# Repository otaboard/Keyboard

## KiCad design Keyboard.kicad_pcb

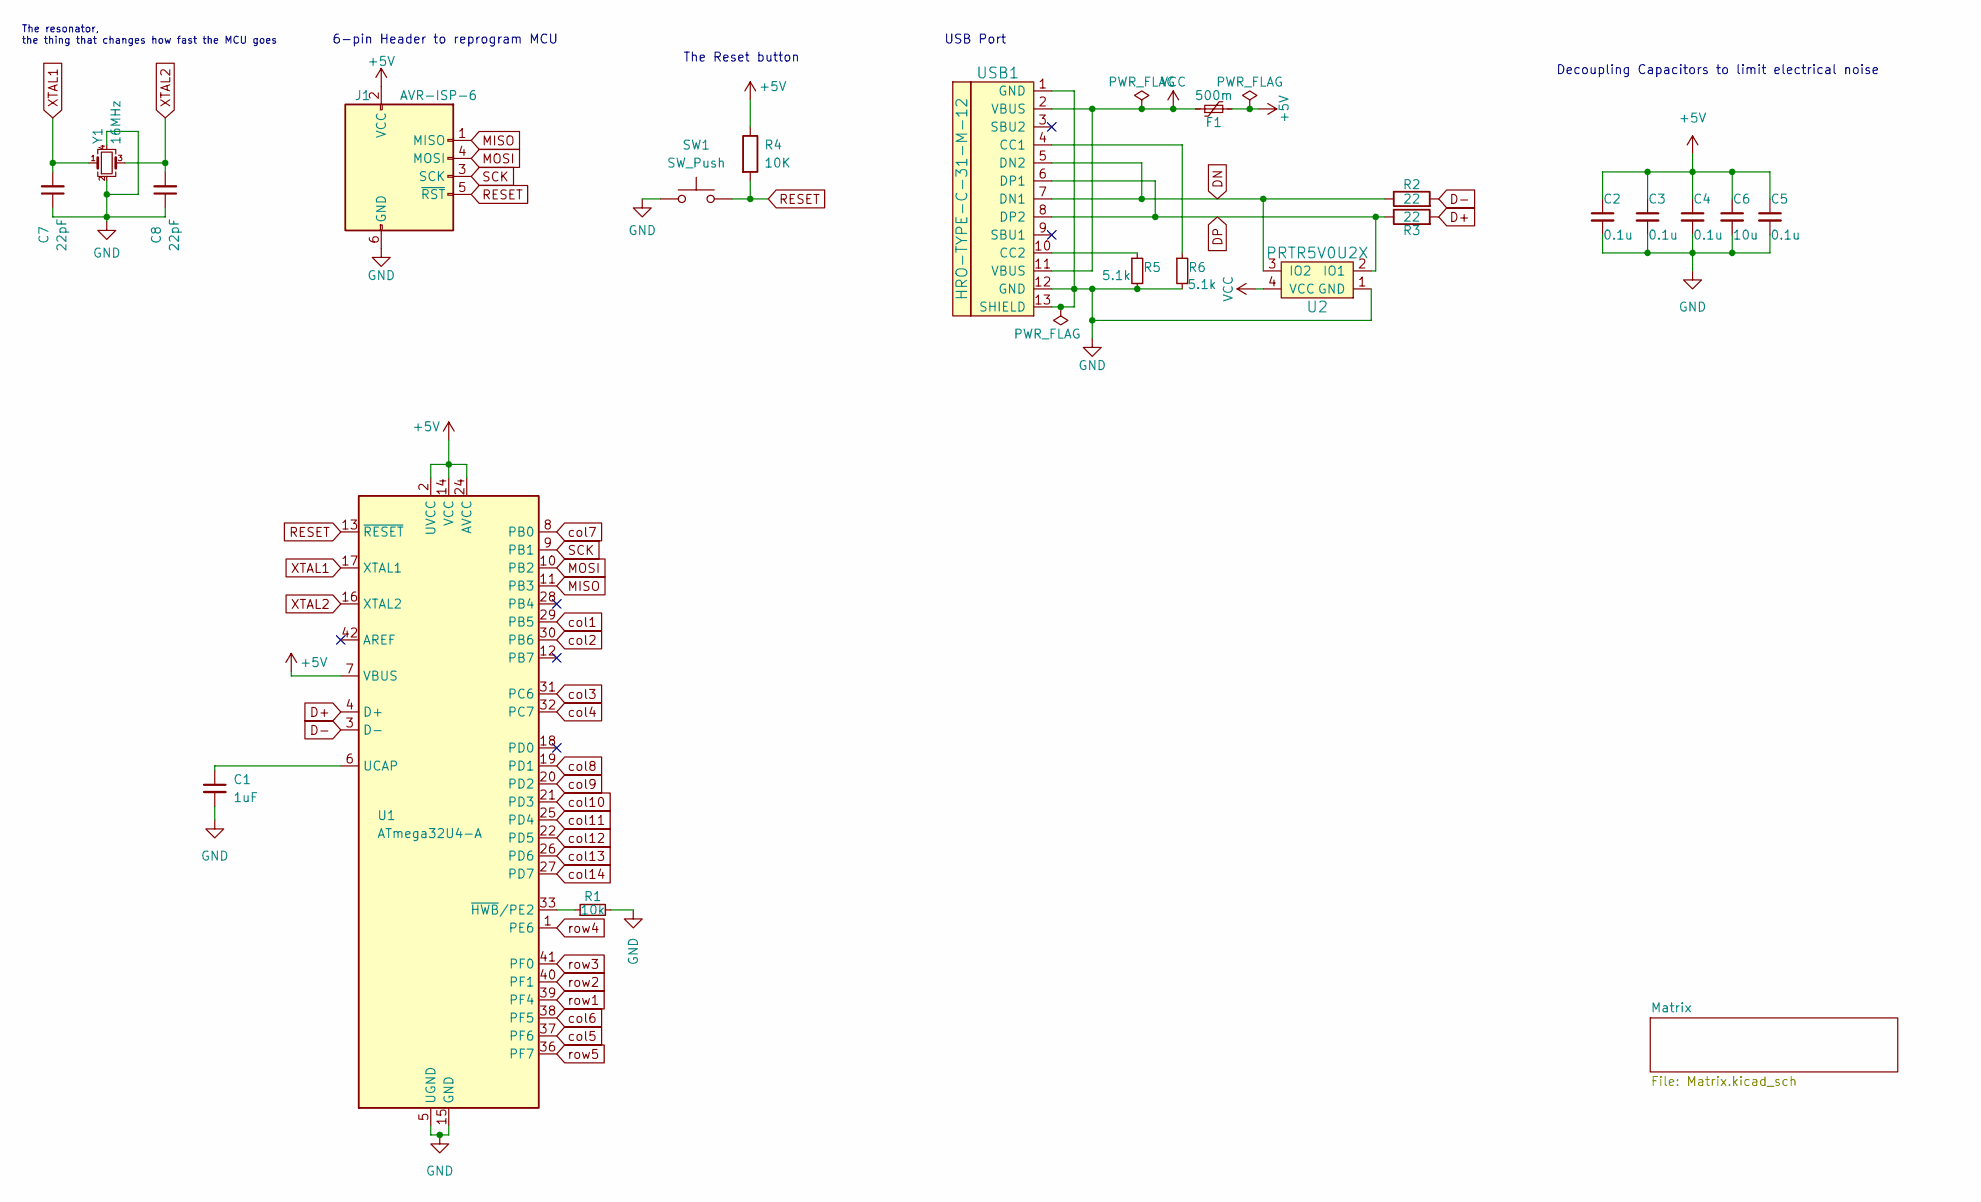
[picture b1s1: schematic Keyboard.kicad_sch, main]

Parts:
C1: 1uF; C_0805_2012Metric_Pad1.18x1.45mm_HandSolder
C2, C3, C4, C5: 0.1u; C_0805_2012Metric_Pad1.18x1.45mm_HandSolder
C6: 10u; C_0805_2012Metric_Pad1.18x1.45mm_HandSolder
C7, C8: 22pF; C_0805_2012Metric_Pad1.18x1.45mm_HandSolder
F1: 500m; Fuse_1206_3216Metric_Pad1.42x1.75mm_HandSolder
J1: AVR-ISP-6; Reset_Pretty-Mask
R1: 10k; R_0805_2012Metric_Pad1.20x1.40mm_HandSolder
R2, R3: 22; R_0805_2012Metric_Pad1.20x1.40mm_HandSolder
R4: 10K; R_0805_2012Metric_Pad1.20x1.40mm_HandSolder
R5, R6: 5.1k; R_0805_2012Metric_Pad1.20x1.40mm_HandSolder
SW1: SW_Push; SW_SPST_SKQG_WithStem
U1: ATmega32U4-A; TQFP-44_10x10mm_P0.8mm
U2: PRTR5V0U2X; SOT143B
USB1: HRO-TYPE-C-31-M-12; HRO-TYPE-C-31-M-12-HandSoldering
Y1: 16MHz; Crystal_SMD_3225-4Pin_3.2x2.5mm_HandSoldering

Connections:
+5V: C2.1, C3.1, C4.1, C5.1, C6.1, F1.2, J1.2 (VCC), R4.1, U1.2 (UVCC), U1.7 (VBUS), U1.14 (VCC), U1.24 (AVCC), U1.34 (VCC), U1.44 (AVCC)
D+: R3.2, U1.4 (D+)
D-: R2.2, U1.3 (D-)
DN: R2.1, U2.3 (IO2), USB1.5 (DN2), USB1.7 (DN1)
DP: R3.1, U2.2 (IO1), USB1.6 (DP1), USB1.8 (DP2)
GND: C1.2, C2.2, C3.2, C4.2, C5.2, C6.2, C7.1, C8.1, J1.6 (GND), R1.2, R5.2, R6.2, SW1.1, U1.5 (UGND), U1.15 (GND), U1.23 (GND), U1.35 (GND), U1.43 (GND), U2.1 (GND), USB1.1 (GND), USB1.12 (GND), USB1.13 (SHIELD), Y1.2, Y1.4
MISO: J1.1 (MISO), U1.11 (PB3)
MOSI: J1.4 (MOSI), U1.10 (PB2)
unnamed: C1.1, U1.6 (UCAP)
unnamed: R1.1, U1.33 (~HWB/PE2)
unnamed: R5.1, USB1.10 (CC2)
unnamed: R6.1, USB1.4 (CC1)
RESET: J1.5 (~RST), R4.2, SW1.2, U1.13 (~RESET)
SCK: J1.3 (SCK), U1.9 (PB1)
VCC: F1.1, U2.4 (VCC), USB1.2 (VBUS), USB1.11 (VBUS)
XTAL1: C7.2, U1.17 (XTAL1), Y1.1
XTAL2: C8.2, U1.16 (XTAL2), Y1.3
col1: U1.29 (PB5); also elsewhere on the board
col2: U1.30 (PB6); also elsewhere on the board
col3: U1.31 (PC6); also elsewhere on the board
col4: U1.32 (PC7); also elsewhere on the board
col5: U1.37 (PF6); also elsewhere on the board
col6: U1.38 (PF5); also elsewhere on the board
col7: U1.8 (PB0); also elsewhere on the board
col8: U1.19 (PD1); also elsewhere on the board
col9: U1.20 (PD2); also elsewhere on the board
col10: U1.21 (PD3); also elsewhere on the board
col11: U1.25 (PD4); also elsewhere on the board
col12: U1.22 (PD5); also elsewhere on the board
col13: U1.26 (PD6); also elsewhere on the board
col14: U1.27 (PD7); also elsewhere on the board
row1: U1.39 (PF4); also elsewhere on the board
row2: U1.40 (PF1); also elsewhere on the board
row3: U1.41 (PF0); also elsewhere on the board
row4: U1.1 (PE6); also elsewhere on the board
row5: U1.36 (PF7); also elsewhere on the board

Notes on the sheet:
6-pin Header to reprogram MCU
USB Port
The resonator, the thing that changes how fast the MCU goes
Decoupling Capacitors to limit electrical noise
The Reset button

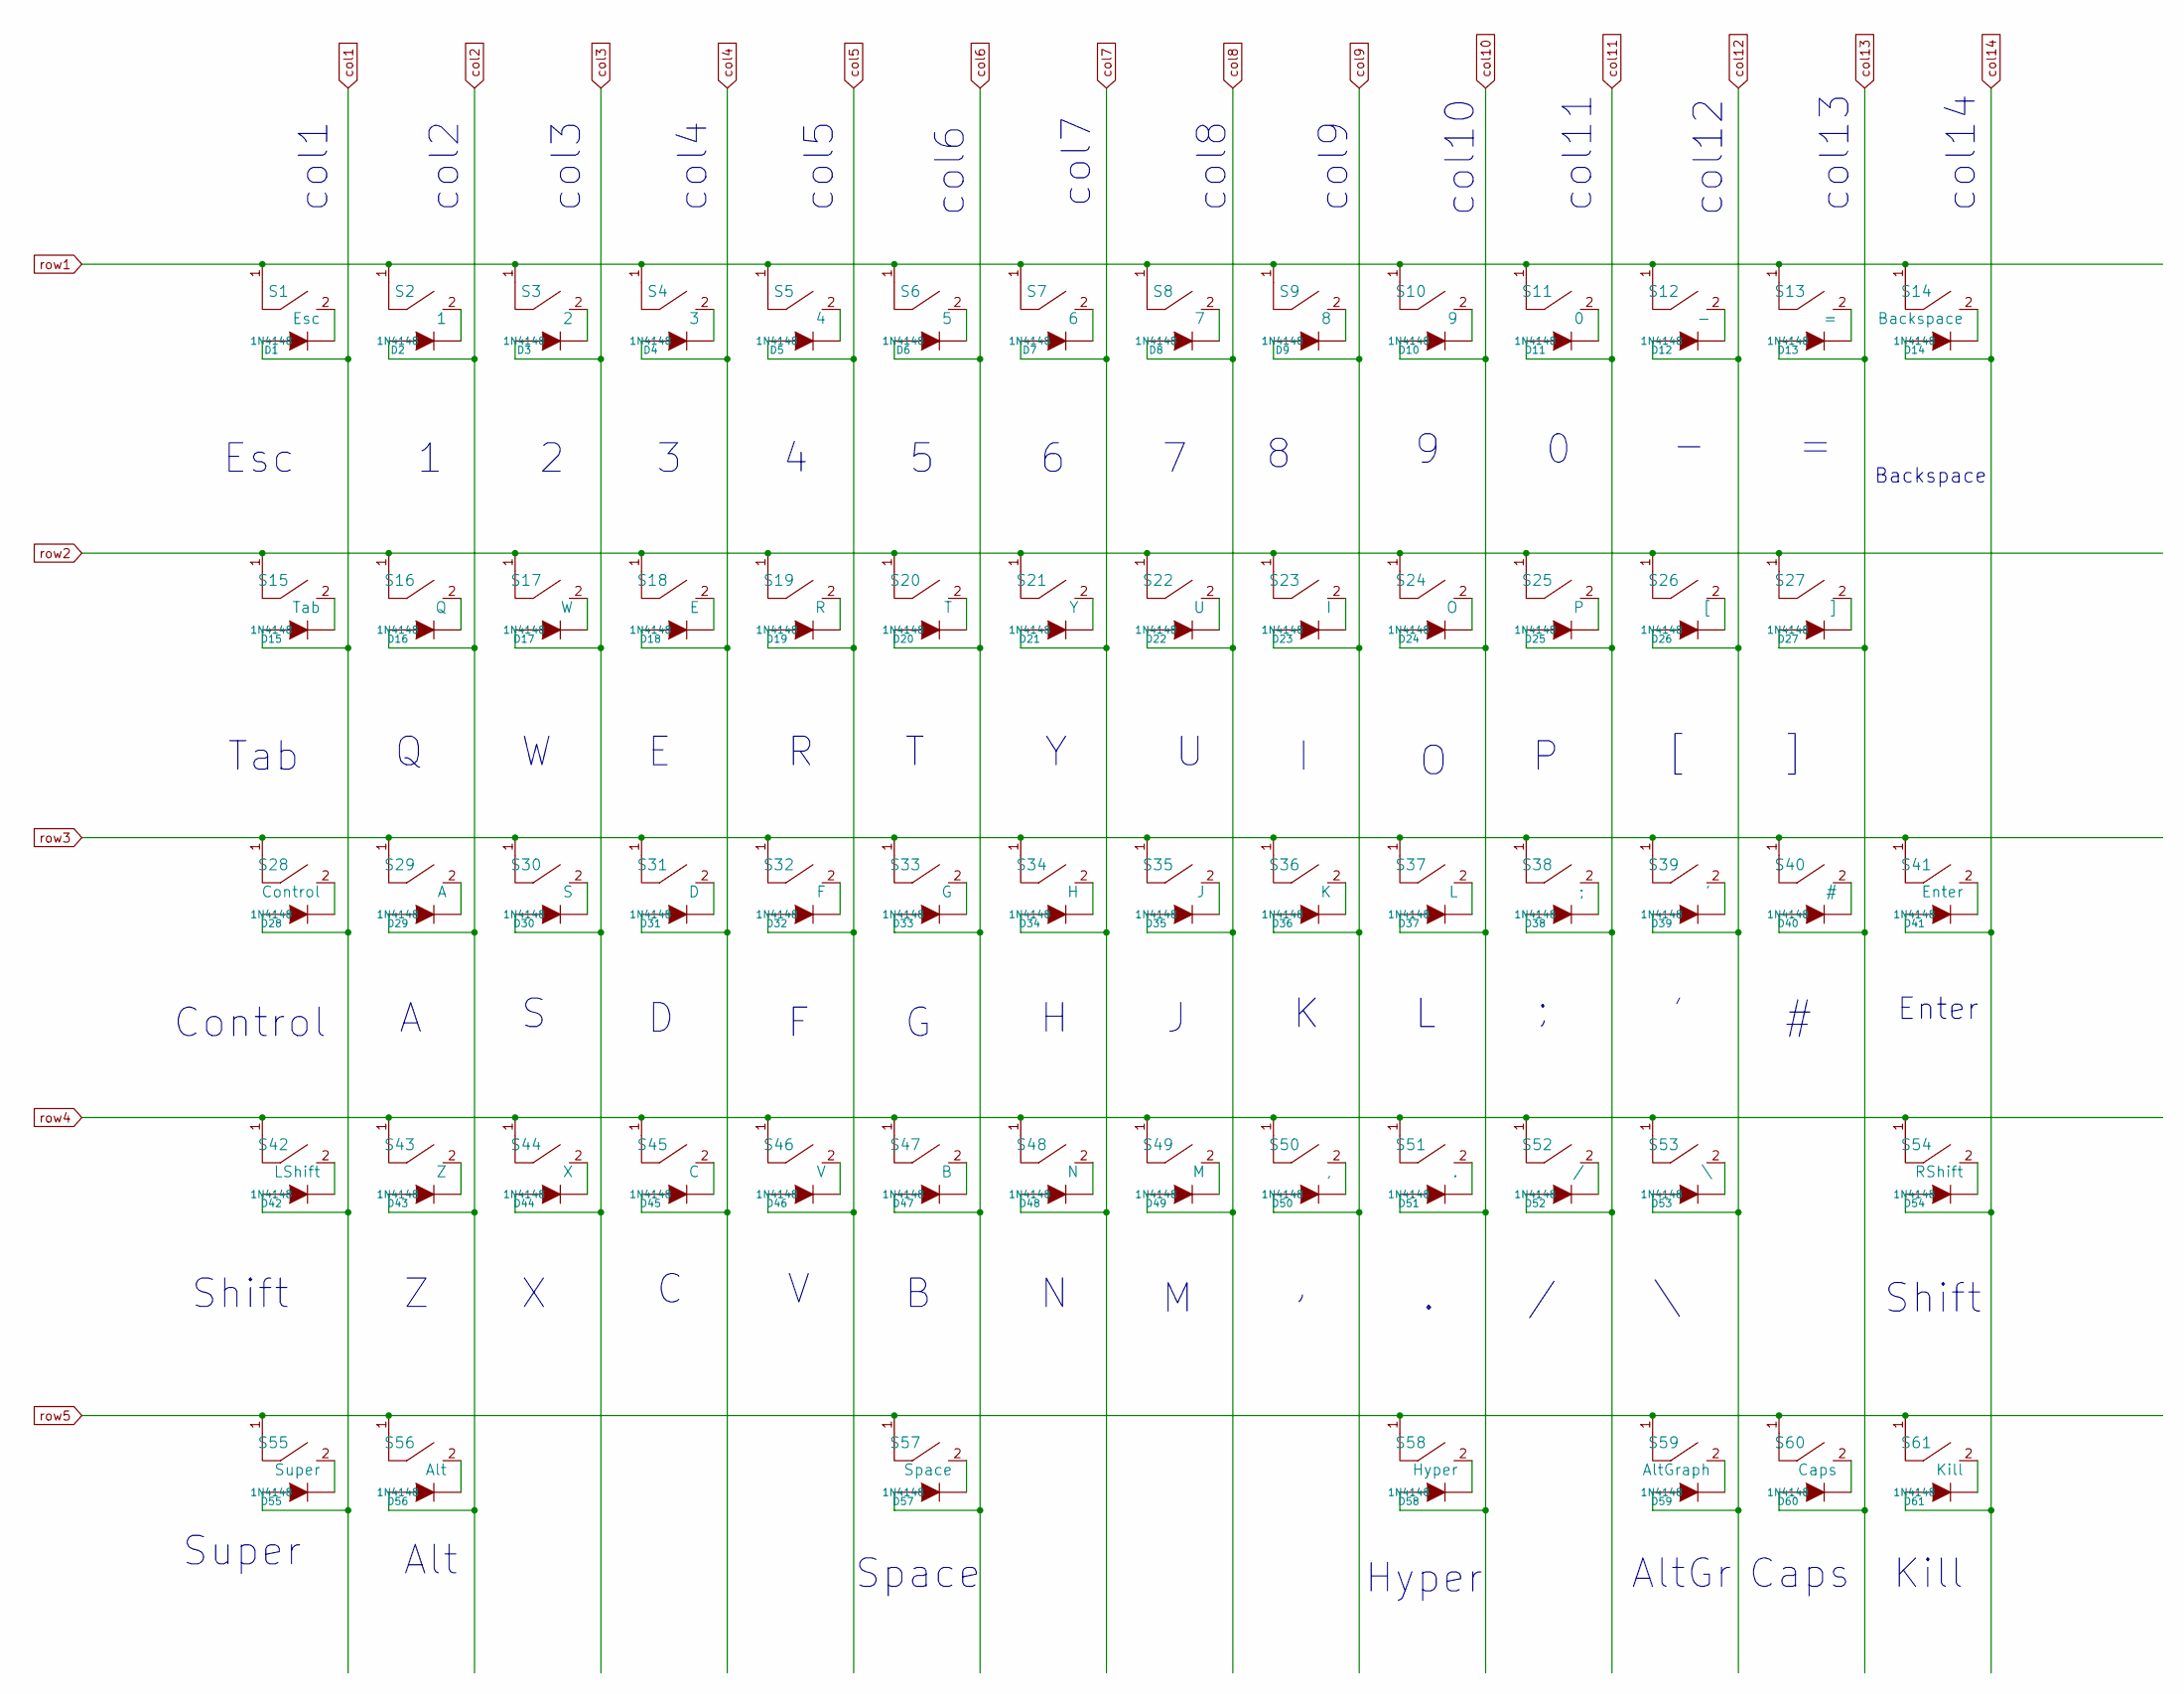
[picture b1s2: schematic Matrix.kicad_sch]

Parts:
D1, D2, D3, D4, D5, D6, D7, D8, D9, D10, D11, D12, D13, D14, D15, D16, D17, D18, D19, D20, D21, D22, D23, D24, D25, D26, D27, D28, D29, D30, D31, D32, D33, D34, D35, D36, D37, D38, D39, D40, D41, D42, D43, D44, D45, D46, D47, D48, D49, D50, D51, D52, D53, D54, D55, D56, D57, D58, D59, D60, D61: 1N4148; D_SOD-123
S1: Esc; MX-1U
S2: 1; MX-1U
S3: 2; MX-1U
S4: 3; MX-1U
S5: 4; MX-1U
S6: 5; MX-1U
S7: 6; MX-1U
S8: 7; MX-1U
S9: 8; MX-1U
S10: 9; MX-1U
S11: 0; MX-1U
S12: -; MX-1U
S13: =; MX-1U
S14: Backspace; MX-2U
S15: Tab; MX-1.5U
S16: Q; MX-1U
S17: W; MX-1U
S18: E; MX-1U
S19: R; MX-1U
S20: T; MX-1U
S21: Y; MX-1U
S22: U; MX-1U
S23: I; MX-1U
S24: O; MX-1U
S25: P; MX-1U
S26: [; MX-1U
S27: ]; MX-1U
S28: Control; MX-1.75U
S29: A; MX-1U
S30: S; MX-1U
S31: D; MX-1U
S32: F; MX-1U
S33: G; MX-1U
S34: H; MX-1U
S35: J; MX-1U
S36: K; MX-1U
S37: L; MX-1U
S38: ;; MX-1U
S39: '; MX-1U
S40: #; MX-1U
S41: Enter; MX-ISO
S42: LShift; MX-2U
S43: Z; MX-1U
S44: X; MX-1U
S45: C; MX-1U
S46: V; MX-1U
S47: B; MX-1U
S48: N; MX-1U
S49: M; MX-1U
S50: ,; MX-1U
S51: .; MX-1U
S52: /; MX-1U
S53: \; MX-1U
S54: RShift; MX-2U
S55: Super; MX-1.75U
S56: Alt; MX-1.75U
S57: Space; MX-6.5U
S58: Hyper; MX-1.75U
S59: AltGraph; MX-1.25U
S60: Caps; MX-1U
S61: Kill; MX-1U

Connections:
unnamed: D1.2 (K), S1.2
unnamed: D2.2 (K), S2.2
unnamed: D3.2 (K), S3.2
unnamed: D4.2 (K), S4.2
unnamed: D5.2 (K), S5.2
unnamed: D6.2 (K), S6.2
unnamed: D7.2 (K), S7.2
unnamed: D8.2 (K), S8.2
unnamed: D9.2 (K), S9.2
unnamed: D10.2 (K), S10.2
unnamed: D11.2 (K), S11.2
unnamed: D12.2 (K), S12.2
unnamed: D13.2 (K), S13.2
unnamed: D14.2 (K), S14.2
unnamed: D15.2 (K), S15.2
unnamed: D16.2 (K), S16.2
unnamed: D17.2 (K), S17.2
unnamed: D18.2 (K), S18.2
unnamed: D19.2 (K), S19.2
unnamed: D20.2 (K), S20.2
unnamed: D21.2 (K), S21.2
unnamed: D22.2 (K), S22.2
unnamed: D23.2 (K), S23.2
unnamed: D24.2 (K), S24.2
unnamed: D25.2 (K), S25.2
unnamed: D26.2 (K), S26.2
unnamed: D27.2 (K), S27.2
unnamed: D28.2 (K), S28.2
unnamed: D29.2 (K), S29.2
unnamed: D30.2 (K), S30.2
unnamed: D31.2 (K), S31.2
unnamed: D32.2 (K), S32.2
unnamed: D33.2 (K), S33.2
unnamed: D34.2 (K), S34.2
unnamed: D35.2 (K), S35.2
unnamed: D36.2 (K), S36.2
unnamed: D37.2 (K), S37.2
unnamed: D38.2 (K), S38.2
unnamed: D39.2 (K), S39.2
unnamed: D40.2 (K), S40.2
unnamed: D41.2 (K), S41.2
unnamed: D42.2 (K), S42.2
unnamed: D43.2 (K), S43.2
unnamed: D44.2 (K), S44.2
unnamed: D45.2 (K), S45.2
unnamed: D46.2 (K), S46.2
unnamed: D47.2 (K), S47.2
unnamed: D48.2 (K), S48.2
unnamed: D49.2 (K), S49.2
unnamed: D50.2 (K), S50.2
unnamed: D51.2 (K), S51.2
unnamed: D52.2 (K), S52.2
unnamed: D53.2 (K), S53.2
unnamed: D54.2 (K), S54.2
unnamed: D55.2 (K), S55.2
unnamed: D56.2 (K), S56.2
unnamed: D57.2 (K), S57.2
unnamed: D58.2 (K), S58.2
unnamed: D59.2 (K), S59.2
unnamed: D60.2 (K), S60.2
unnamed: D61.2 (K), S61.2
col1: D1.1 (A), D15.1 (A), D28.1 (A), D42.1 (A), D55.1 (A); also elsewhere on the board
col2: D2.1 (A), D16.1 (A), D29.1 (A), D43.1 (A), D56.1 (A); also elsewhere on the board
col3: D3.1 (A), D17.1 (A), D30.1 (A), D44.1 (A); also elsewhere on the board
col4: D4.1 (A), D18.1 (A), D31.1 (A), D45.1 (A); also elsewhere on the board
col5: D5.1 (A), D19.1 (A), D32.1 (A), D46.1 (A); also elsewhere on the board
col6: D6.1 (A), D20.1 (A), D33.1 (A), D47.1 (A), D57.1 (A); also elsewhere on the board
col7: D7.1 (A), D21.1 (A), D34.1 (A), D48.1 (A); also elsewhere on the board
col8: D8.1 (A), D22.1 (A), D35.1 (A), D49.1 (A); also elsewhere on the board
col9: D9.1 (A), D23.1 (A), D36.1 (A), D50.1 (A); also elsewhere on the board
col10: D10.1 (A), D24.1 (A), D37.1 (A), D51.1 (A), D58.1 (A); also elsewhere on the board
col11: D11.1 (A), D25.1 (A), D38.1 (A), D52.1 (A); also elsewhere on the board
col12: D12.1 (A), D26.1 (A), D39.1 (A), D53.1 (A), D59.1 (A); also elsewhere on the board
col13: D13.1 (A), D27.1 (A), D40.1 (A), D60.1 (A); also elsewhere on the board
col14: D14.1 (A), D41.1 (A), D54.1 (A), D61.1 (A); also elsewhere on the board
row1: S1.1, S2.1, S3.1, S4.1, S5.1, S6.1, S7.1, S8.1, S9.1, S10.1, S11.1, S12.1, S13.1, S14.1; also elsewhere on the board
row2: S15.1, S16.1, S17.1, S18.1, S19.1, S20.1, S21.1, S22.1, S23.1, S24.1, S25.1, S26.1, S27.1; also elsewhere on the board
row3: S28.1, S29.1, S30.1, S31.1, S32.1, S33.1, S34.1, S35.1, S36.1, S37.1, S38.1, S39.1, S40.1, S41.1; also elsewhere on the board
row4: S42.1, S43.1, S44.1, S45.1, S46.1, S47.1, S48.1, S49.1, S50.1, S51.1, S52.1, S53.1, S54.1; also elsewhere on the board
row5: S55.1, S56.1, S57.1, S58.1, S59.1, S60.1, S61.1; also elsewhere on the board

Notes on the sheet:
Hyper
Kill
Control
col13
col6
Space
col1
col12
Caps
AltGr
col7
Shift
col2
col10
col3
col14
Tab
col8
Esc
Super
col11
Enter
Backspace
Alt
col4
col9
col5

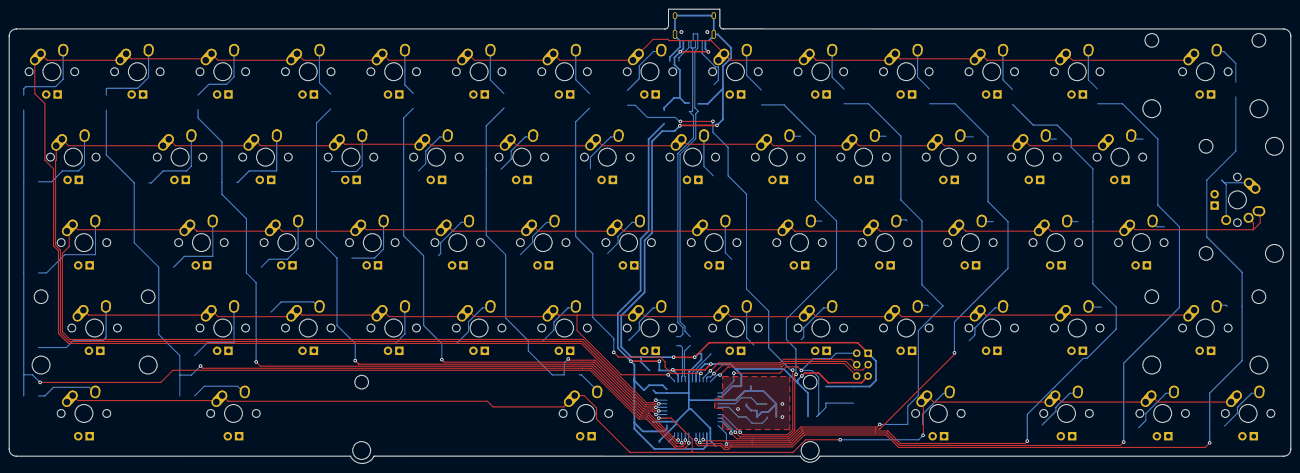
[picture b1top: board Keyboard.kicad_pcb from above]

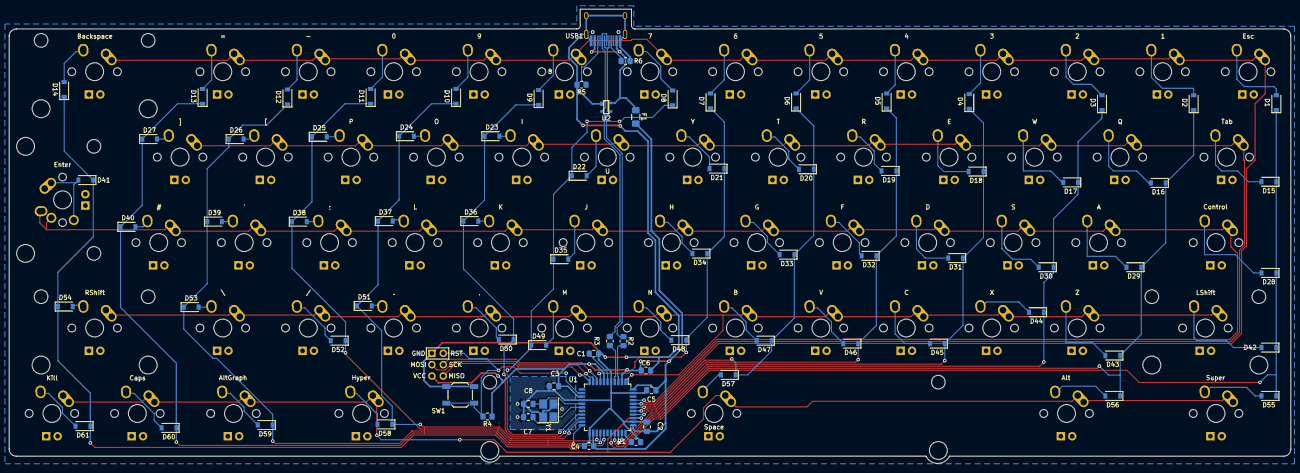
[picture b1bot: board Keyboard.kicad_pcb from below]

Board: 2 copper layers, 285.8 x 101.3 mm, 143 parts (82 on the bottom side), 97 nets.

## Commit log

2022-08-09 Added Kicad files
2022-08-09 Added a TQFP pakcage version
2022-08-09 Created Matrix file and added row and column wires
2022-08-09 Fixed column and row labels on Matrix
2022-08-10 Added key labels signifiying where each key will go to the matrix
2022-08-10 Added all remaining switches and annotations to the matrix
2022-08-11 Connected some columns to MCU and cleaned up main schema
2022-08-11 Assigned footprints and connected all rows and columns to MCU
2022-08-12 Created PCB and moved switches, diodes, MCU, Type-C connector, and other components to their correct locations
2022-08-12 Drew all edge cuts
2022-08-12 Fixed the spacebar's stabiliser holes popping out of the PCB
2022-08-12 Added all row and column tracks ( exc. col8 )
2022-08-12 Added libraries
2022-08-13 Connected D- and D+ on MCU to both D- and both D+ on Type-C connector
2022-08-13 Connected USB data lines and power lines to MCU
2022-08-13 Added buses for like tracks and changed 5V track layout
2022-08-14 Connected all columns and rows to MCU and removed redundant vias
2022-08-14 Connected reset button and ISP header to MCU, added ground pour on B.Cu, and updated footprints
2022-08-14 Created FrontGroundPour, isolated crystal from rest of PCB, and added vias between pours
2022-08-14 Added ferrite bead to prevent ESDs
2022-08-14 Changed PCB thickness to 1.55mm
2022-08-18 Moved USB-C to fit GH60 cases
